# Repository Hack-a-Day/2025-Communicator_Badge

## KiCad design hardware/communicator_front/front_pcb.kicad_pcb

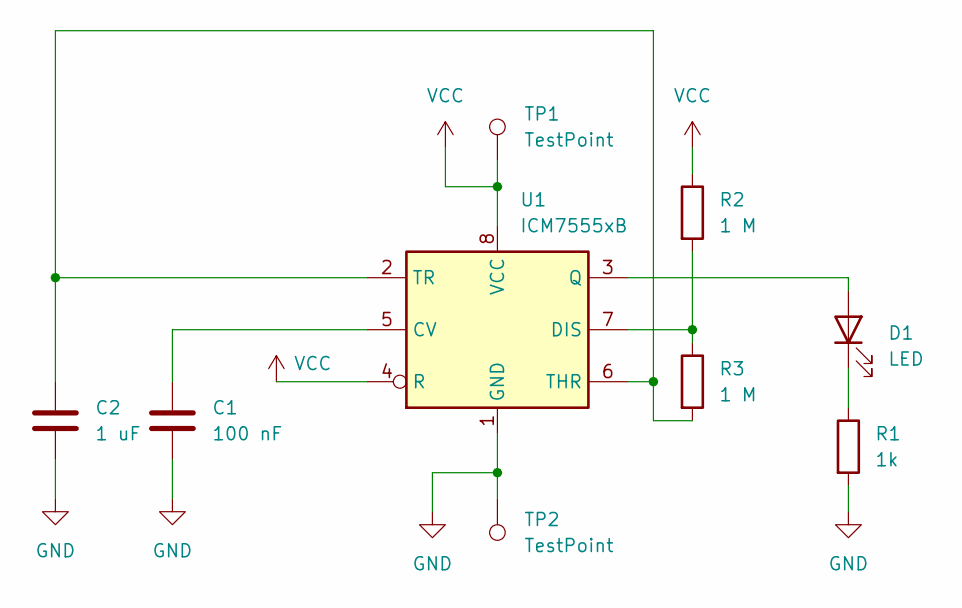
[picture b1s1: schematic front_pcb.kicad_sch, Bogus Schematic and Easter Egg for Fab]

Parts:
C1: 100 nF; C_0805_2012Metric_Pad1.18x1.45mm_HandSolder
C2: 1 uF; C_0805_2012Metric_Pad1.18x1.45mm_HandSolder
D1: LED; LED_0805_2012Metric_Pad1.15x1.40mm_HandSolder
R1: 1k; R_0805_2012Metric_Pad1.20x1.40mm_HandSolder
R2, R3: 1 M; R_0805_2012Metric_Pad1.20x1.40mm_HandSolder
TP1, TP2: TestPoint; TestPoint_Pad_2.5x2.5mm
U1: ICM7555xB; SOIC-8_3.9x4.9mm_P1.27mm

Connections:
GND: C1.2, C2.2, R1.2, TP2.1, U1.1 (GND)
unnamed: D1.2 (A), U1.3 (Q)
unnamed: D1.1 (K), R1.1
unnamed: C1.1, U1.5 (CV)
unnamed: R2.2, R3.1, U1.7 (DIS)
unnamed: C2.1, R3.2, U1.2 (TR), U1.6 (THR)
VCC: R2.1, TP1.1, U1.4 (R), U1.8 (VCC)

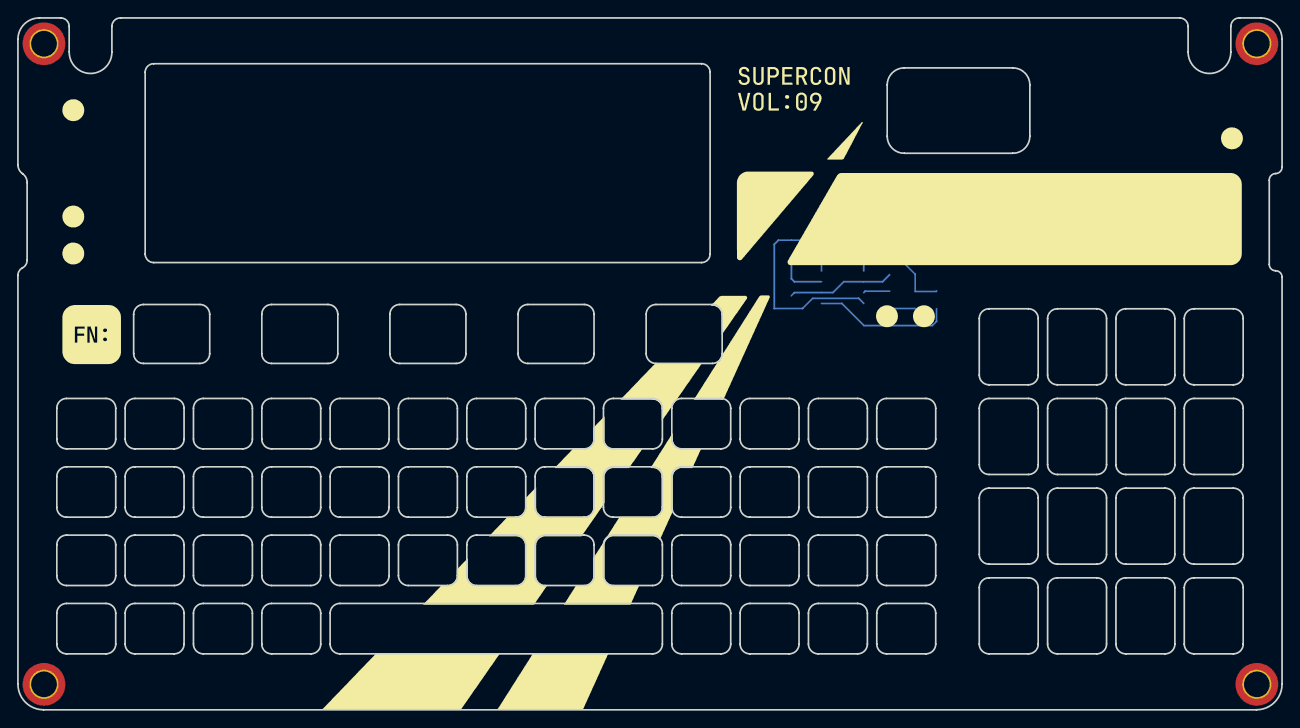
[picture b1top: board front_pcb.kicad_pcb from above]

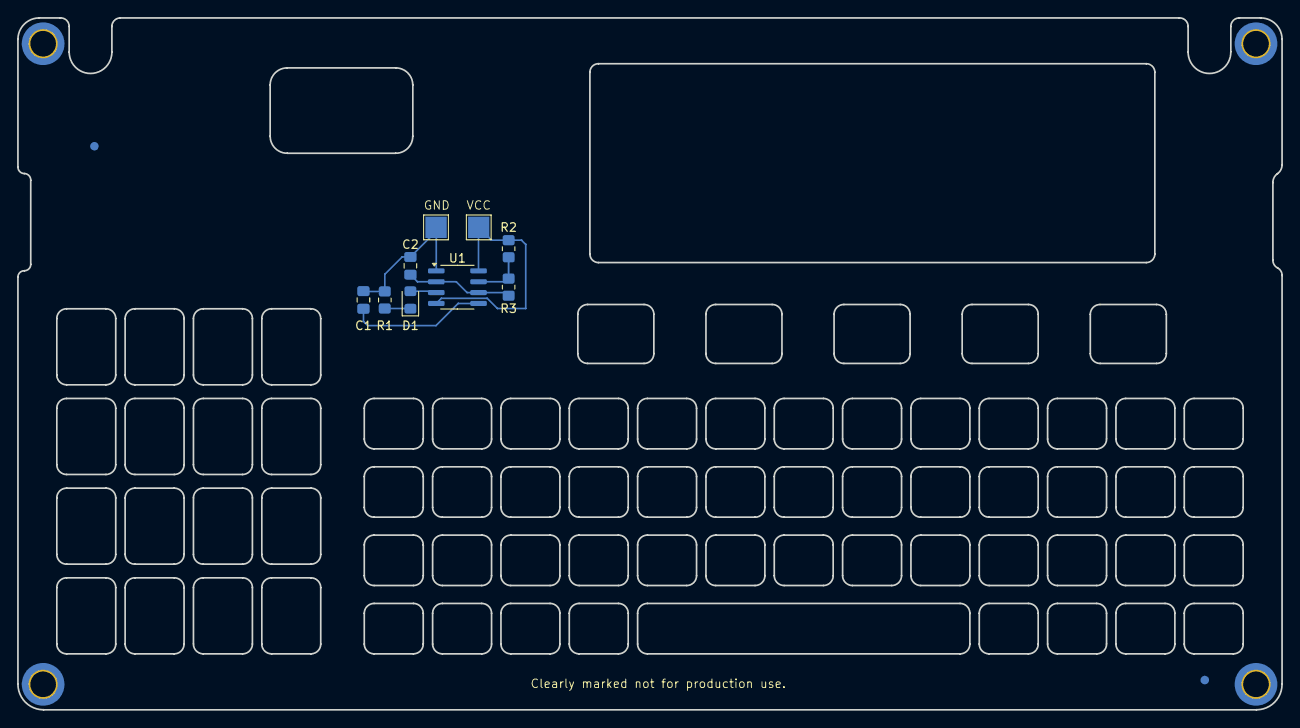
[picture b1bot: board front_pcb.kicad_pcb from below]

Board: 2 copper layers, 148.0 x 81.0 mm, 9 parts (9 on the bottom side), 7 nets.

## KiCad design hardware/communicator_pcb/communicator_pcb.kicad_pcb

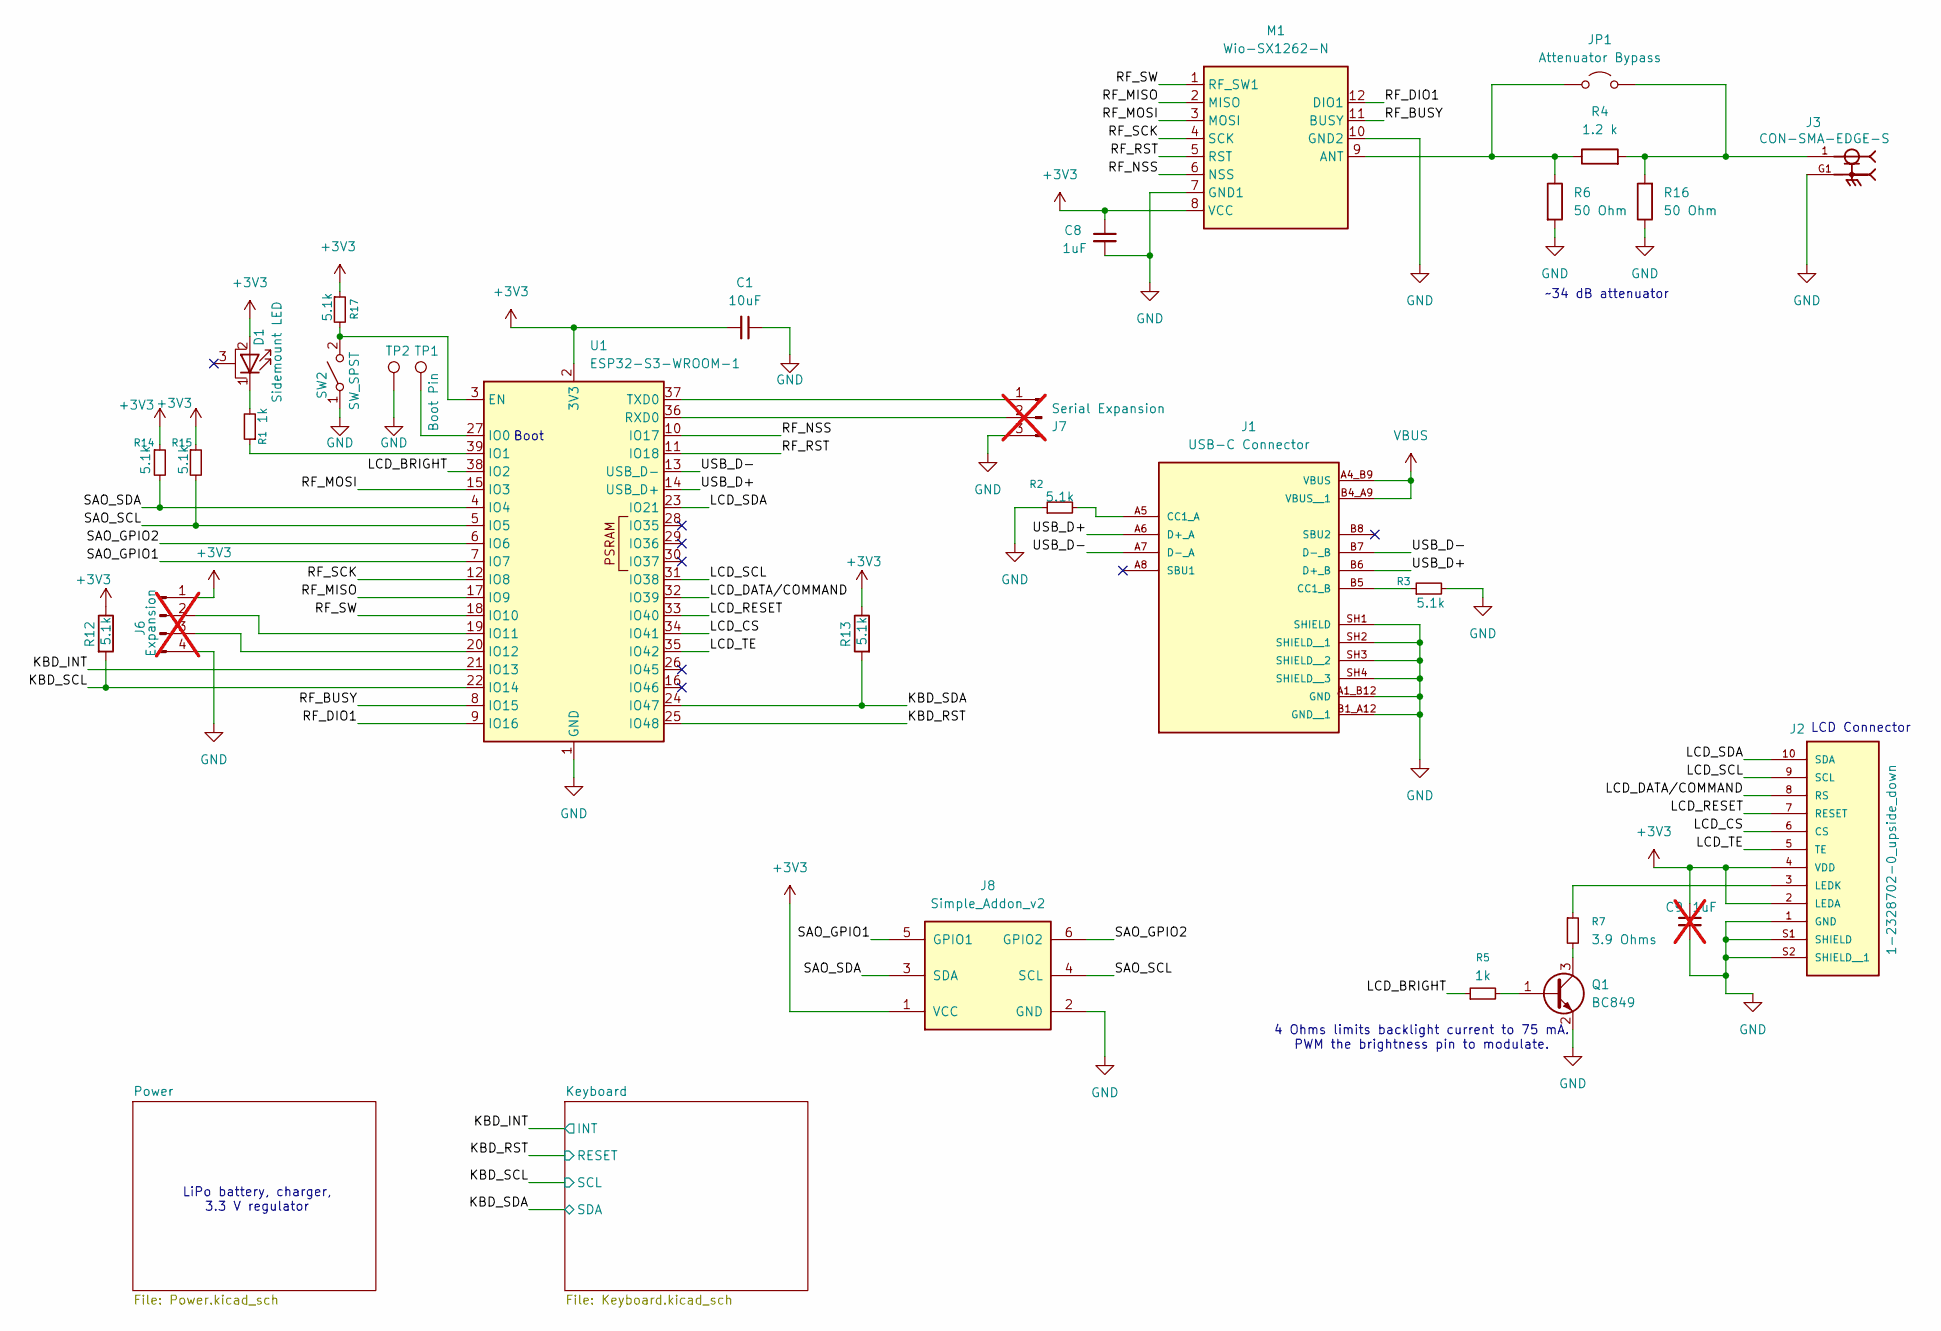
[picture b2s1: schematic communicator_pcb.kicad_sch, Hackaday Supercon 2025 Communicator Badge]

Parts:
C1: 10uF; C_0603_1608Metric
C8: 1uF; C_0603_1608Metric
C9: 1uF; C_0603_1608Metric; not fitted
D1: Sidemount LED; WL-SMSW_1204
J1: USB-C Connector; AMPHENOL_12402012E212A; PARTREV 4
J2: 1-2328702-0_upside_down; TE_1-2328702-0; PARTREV 5
J3: CON-SMA-EDGE-S; RFSOLUTIONS_CON-SMA-EDGE-S; PARTREV 1
J6: Expansion; PinSocket_1x04_P2.54mm_Vertical; not fitted
J7: Serial Expansion; PinHeader_1x03_P2.54mm_Vertical; not fitted
J8: Simple_Addon_v2; Simple_Addon_v2-BADGE-2x3
JP1: Attenuator Bypass; SolderJumper-2_P1.3mm_Open_RoundedPad1.0x1.5mm
M1: Wio-SX1262-N; Wio1262-N
Q1: BC849; SOT-23
R1, R5: 1k; R_0603_1608Metric
R2, R3, R12, R13, R14, R15, R17: 5.1k; R_0603_1608Metric
R4: 1.2 k; R_0603_1608Metric_Pad0.98x0.95mm_HandSolder
R6, R16: 50 Ohm; R_0603_1608Metric_Pad0.98x0.95mm_HandSolder
R7: 3.9 Ohms; R_0603_1608Metric
SW2: SW_SPST; SW_Tactile_SPST_NO_Straight_CK_PTS636Sx25SMTRLFS
TP1: Boot Pin; TestPoint_Pad_D1.5mm
TP2: TestPoint; TestPoint_Pad_D1.5mm
U1: ESP32-S3-WROOM-1

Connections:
+3V3: C1.2, C8.1, C9.1, D1.2 (A), J2.2 (LEDA), J2.4 (VDD), J6.1, J8.1 (VCC), M1.8 (VCC), R12.1, R13.1, R14.1, R15.1, R17.1, U1.2 (3V3); also elsewhere on the board
/KBD_INT: U1.21 (IO13); also elsewhere on the board
/KBD_RST: U1.25 (IO48); also elsewhere on the board
/KBD_SCL: R12.2, U1.22 (IO14); also elsewhere on the board
/KBD_SDA: R13.2, U1.24 (IO47); also elsewhere on the board
/LCD_BRIGHT: R5.1, U1.38 (IO2)
/LCD_CS: J2.6 (CS), U1.34 (IO41)
/LCD_DATA/COMMAND: J2.8 (RS), U1.32 (IO39)
/LCD_RESET: J2.7 (RESET), U1.33 (IO40)
/LCD_SCL: J2.9 (SCL), U1.31 (IO38)
/LCD_SDA: J2.10 (SDA), U1.23 (IO21)
/LCD_TE: J2.5 (TE), U1.35 (IO42)
/RF_BUSY: M1.11 (BUSY), U1.8 (IO15)
/RF_DIO1: M1.12 (DIO1), U1.9 (IO16)
/RF_MISO: M1.2 (MISO), U1.17 (IO9)
/RF_MOSI: M1.3 (MOSI), U1.15 (IO3)
/RF_NSS: M1.6 (NSS), U1.10 (IO17)
/RF_RST: M1.5 (RST), U1.11 (IO18)
/RF_SCK: M1.4 (SCK), U1.12 (IO8)
/RF_SW: M1.1 (RF_SW1), U1.18 (IO10)
/SAO_GPIO1: J8.5 (GPIO1), U1.7 (IO7)
/SAO_GPIO2: J8.6 (GPIO2), U1.6 (IO6)
/SAO_SCL: J8.4 (SCL), R15.2, U1.5 (IO5)
/SAO_SDA: J8.3 (SDA), R14.2, U1.4 (IO4)
/USB_D+: J1.A6 (D+_A), J1.B6 (D+_B), U1.14 (USB_D+)
/USB_D-: J1.A7 (D-_A), J1.B7 (D-_B), U1.13 (USB_D-)
GND: C1.1, C8.2, C9.2, J1.A1_B12 (GND), J1.B1_A12 (GND__1), J1.SH1 (SHIELD), J1.SH2 (SHIELD__1), J1.SH3 (SHIELD__2), J1.SH4 (SHIELD__3), J2.1 (GND), J2.S1 (SHIELD), J2.S2 (SHIELD__1), J3.G1, J3.G2, J3.G3, J3.G4, J6.4, J7.3, J8.2 (GND), M1.7 (GND1), M1.10 (GND2), Q1.2 (E), R2.1, R3.2, R6.2, R16.1, SW2.1 (A), TP2.1, U1.1 (GND), U1.40 (GND), U1.41 (GND); also elsewhere on the board
unnamed: D1.1 (K), R1.2
unnamed: J1.A5 (CC1_A), R2.2
unnamed: J1.B5 (CC1_B), R3.1
unnamed: J2.3 (LEDK), R7.1
unnamed: J6.2, U1.19 (IO11)
unnamed: J6.3, U1.20 (IO12)
unnamed: J7.1, U1.37 (TXD0)
unnamed: J7.2, U1.36 (RXD0)
unnamed: JP1.1 (A), M1.9 (ANT), R4.1, R6.1
unnamed: J3.1, JP1.2 (B), R4.2, R16.2
unnamed: Q1.1 (B), R5.2
unnamed: Q1.3 (C), R7.2
unnamed: R17.2, SW2.2 (B), U1.3 (EN)
unnamed: TP1.1, U1.27 (IO0)
unnamed: R1.1, U1.39 (IO1)
VBUS: J1.A4_B9 (VBUS), J1.B4_A9 (VBUS__1); also elsewhere on the board

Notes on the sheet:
~34 dB attenuator
LCD Connector
LiPo battery, charger, 3.3 V regulator
Boot
4 Ohms limits backlight current to 75 mA. PWM the brightness pin to modulate.

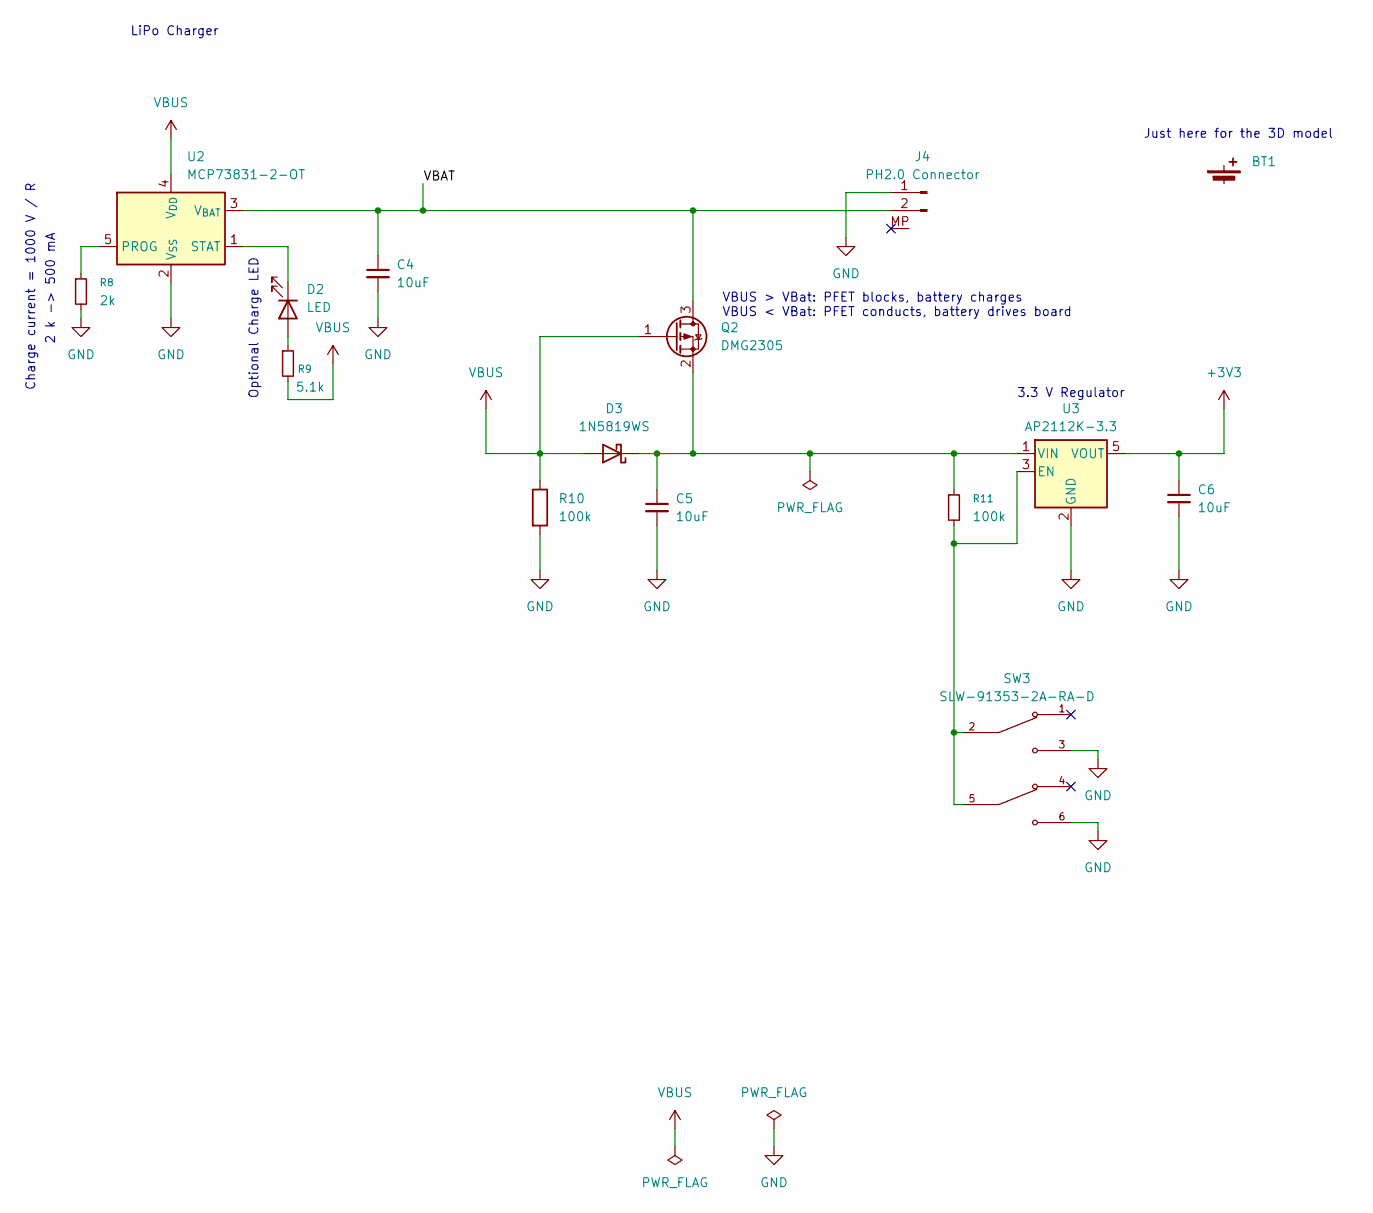
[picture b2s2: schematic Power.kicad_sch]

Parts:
BT1: BatteryMockup
C4, C5, C6: 10uF; C_0603_1608Metric
D2: LED; LED_0805_2012Metric
D3: 1N5819WS; D_SOD-323
J4: PH2.0 Connector; JST_PH_S2B-PH-SM4-TB_1x02-1MP_P2.00mm_Horizontal
Q2: DMG2305; SOT-23
R8: 2k; R_0603_1608Metric
R9: 5.1k; R_0603_1608Metric
R10, R11: 100k; R_0603_1608Metric
SW3: SLW-91353-2A-RA-D; SW_SLW-91353-2A-RA-D; PARTREV 1.01
U2: MCP73831-2-OT; SOT-23-5
U3: AP2112K-3.3; SOT-23-5

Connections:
+3V3: C6.1, U3.5 (VOUT); also elsewhere on the board
/Power/VBAT: C4.1, J4.2, Q2.3 (D), U2.3 (V_{BAT})
GND: C4.2, C5.2, C6.2, J4.1, R8.2, R10.2, SW3.3, SW3.6, U2.2 (V_{SS}), U3.2 (GND); also elsewhere on the board
unnamed: D2.2 (A), R9.1
unnamed: D2.1 (K), U2.1 (STAT)
unnamed: C5.1, D3.1 (K), Q2.2 (S), R11.1, U3.1 (VIN)
unnamed: R8.1, U2.5 (PROG)
unnamed: R11.2, SW3.2, SW3.5, U3.3 (EN)
VBUS: D3.2 (A), Q2.1 (G), R9.2, R10.1, U2.4 (V_{DD}); also elsewhere on the board

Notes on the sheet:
Optional Charge LED
Just here for the 3D model
VBUS > VBat: PFET blocks, battery charges VBUS < VBat: PFET conducts, battery drives board
Charge current = 1000 V / R
2 k -> 500 mA
LiPo Charger
3.3 V Regulator

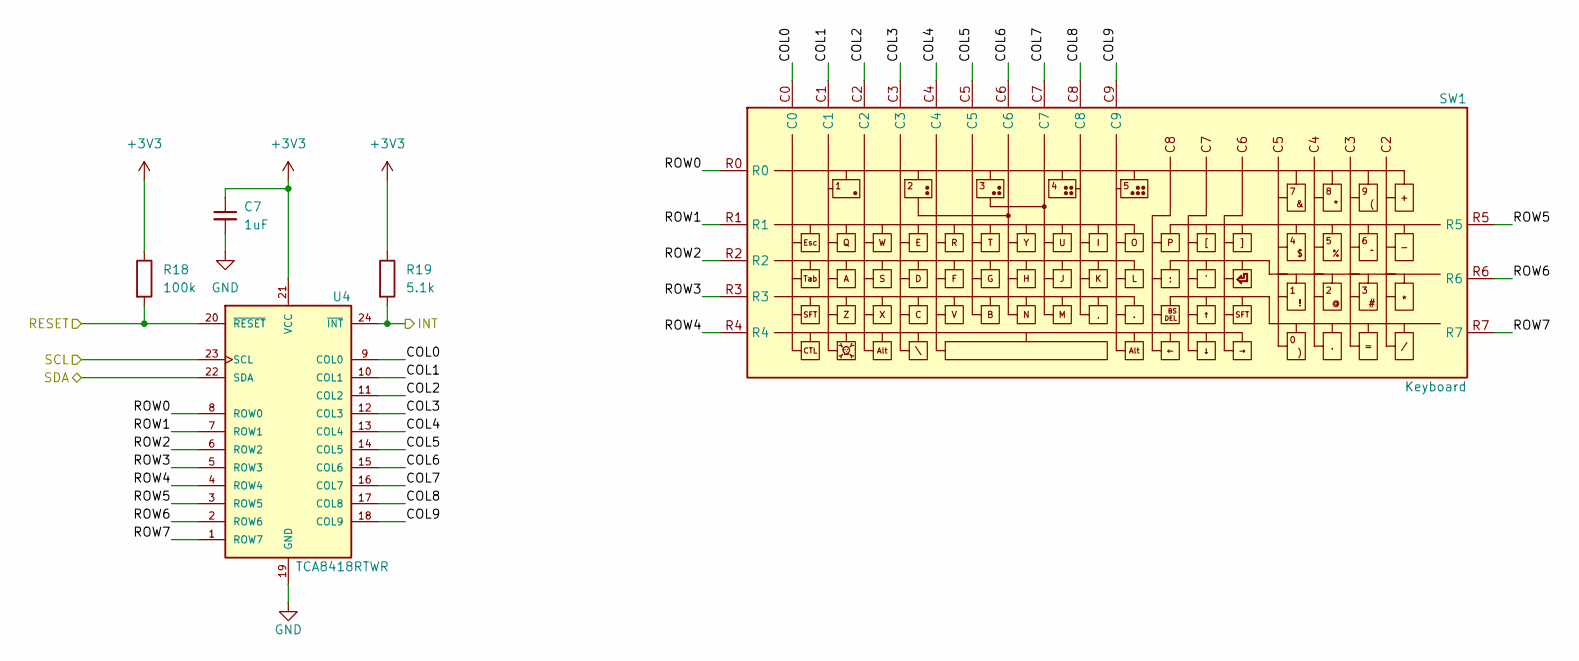
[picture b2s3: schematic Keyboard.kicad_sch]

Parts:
C7: 1uF; C_0603_1608Metric
R18: 100k; R_0603_1608Metric
R19: 5.1k; R_0603_1608Metric
SW1: Keyboard
U4: TCA8418RTWR; VQFN-24-1EP_4x4mm_P0.5mm_EP2.5x2.5mm; PARTREV G

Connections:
+3V3: C7.1, R18.1, R19.1, U4.21 (VCC); also elsewhere on the board
/KBD_INT: R19.2, U4.24 (~INT); also elsewhere on the board
/KBD_RST: R18.2, U4.20 (~RESET); also elsewhere on the board
/KBD_SCL: U4.23 (SCL); also elsewhere on the board
/KBD_SDA: U4.22 (SDA); also elsewhere on the board
/Keyboard/COL0: SW1.C0, U4.9 (COL0)
/Keyboard/COL1: SW1.C1, U4.10 (COL1)
/Keyboard/COL2: SW1.C2, U4.11 (COL2)
/Keyboard/COL3: SW1.C3, U4.12 (COL3)
/Keyboard/COL4: SW1.C4, U4.13 (COL4)
/Keyboard/COL5: SW1.C5, U4.14 (COL5)
/Keyboard/COL6: SW1.C6, U4.15 (COL6)
/Keyboard/COL7: SW1.C7, U4.16 (COL7)
/Keyboard/COL8: SW1.C8, U4.17 (COL8)
/Keyboard/COL9: SW1.C9, U4.18 (COL9)
/Keyboard/ROW0: SW1.R0, U4.8 (ROW0)
/Keyboard/ROW1: SW1.R1, U4.7 (ROW1)
/Keyboard/ROW2: SW1.R2, U4.6 (ROW2)
/Keyboard/ROW3: SW1.R3, U4.5 (ROW3)
/Keyboard/ROW4: SW1.R4, U4.4 (ROW4)
/Keyboard/ROW5: SW1.R5, U4.3 (ROW5)
/Keyboard/ROW6: SW1.R6, U4.2 (ROW6)
/Keyboard/ROW7: SW1.R7, U4.1 (ROW7)
GND: C7.2, U4.19 (GND), U4.25 (EP); also elsewhere on the board

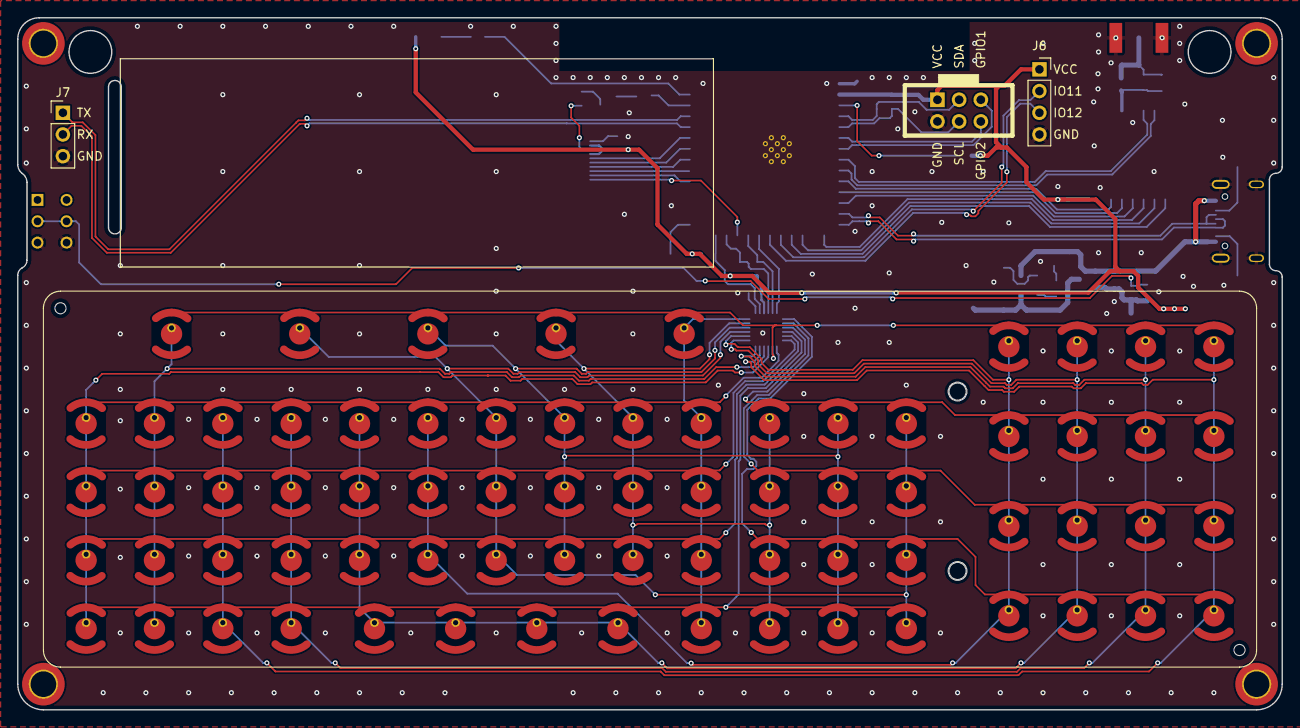
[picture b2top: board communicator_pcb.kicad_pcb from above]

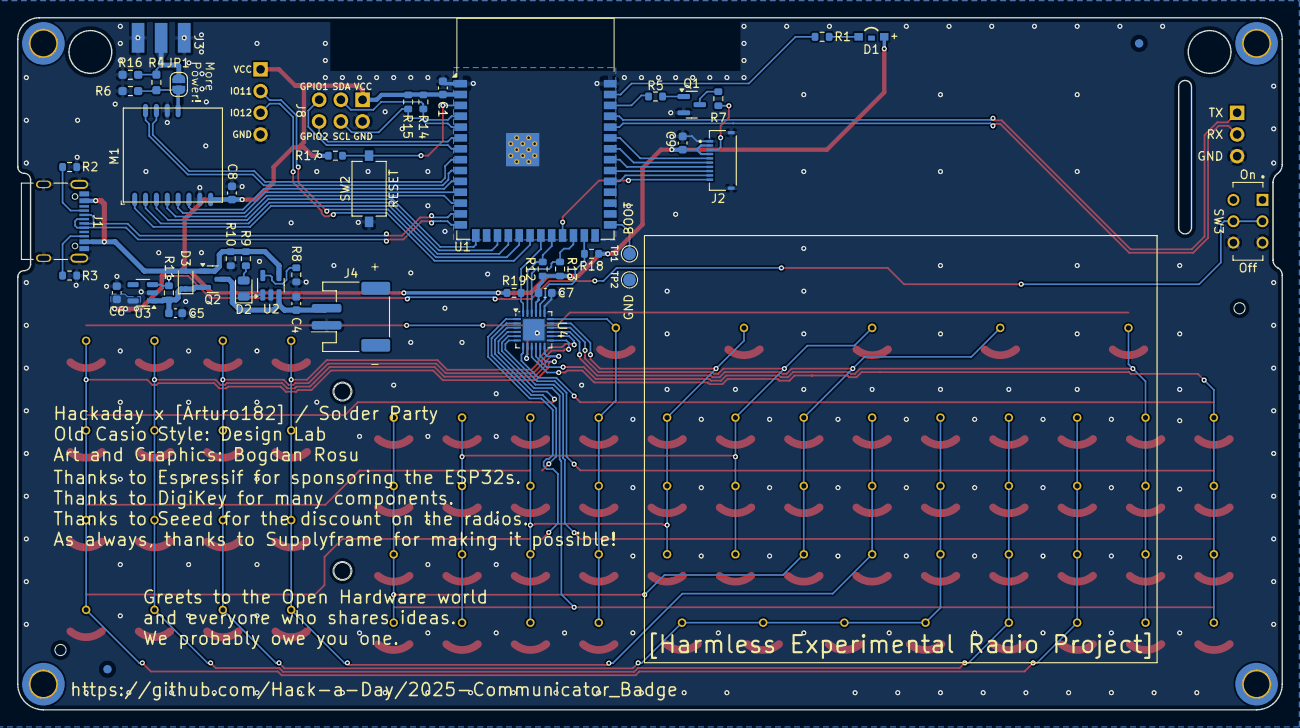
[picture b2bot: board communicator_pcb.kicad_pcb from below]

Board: 2 copper layers, 148.0 x 81.0 mm, 50 parts (46 on the bottom side), 67 nets.

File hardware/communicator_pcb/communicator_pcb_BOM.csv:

Reference	Qty	Value	DNP	Footprint	Part	Datasheet	
C1,C4,C5,C6	4	10uF		Capacitor_SMD:C_0603_1608Metric		~	
C7,C8	2	1uF		Capacitor_SMD:C_0603_1608Metric		~	
D1	1	Sidemount LED		wurth_led_155124YS73200:WL-SMSW_1204	https://www.digikey.de/en/products/detail/w%C3%BCrth-elektro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	https://www.we-online.com/components/products/datasheet/1551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	
D2	1	LED		LED_SMD:LED_0805_2012Metric		~	
D3	1	1N5819WS		Diode_SMD:D_SOD-323	https://www.digikey.de/en/products/detail/shenzhen-slkormicr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	https://datasheet.lcsc.com/lcsc/2204281430_Guangdong-Hottech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	
J1	1	USB-C Connector		amphenol_12402012E212A:AMPHENOL_12402012E212A	https://www.digikey.de/en/products/detail/amphenol-cs-commer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	https://cdn.amphenol-cs.com/media/wysiwyg/files/drawing/1240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	
J2	1	1-2328702-0_upside_down		TE_1-2328702-0:TE_1-2328702-0	https://www.digikey.de/en/products/detail/te-connectivity-am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		
J3	1	CON-SMA-EDGE-S		CON_SMA_EDGE_S:RFSOLUTIONS_CON-SMA-EDGE-S			
J4	1	PH2.0 Connector		Connector_JST:JST_PH_S2B-PH-SM4-TB_1x02-1MP_P2.00mm_Horizontal	https://www.digikey.com/en/products/detail/jst-sales-america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	https://www.jst-mfg.com/product/pdf/eng/ePH.pdf	
J8	1	Simple_Addon_v2		Simple_Addon_v2:Simple_Addon_v2-BADGE-2x3	Where are we getting these?  Can we get the nice shrouded onew?	https://hackaday.io/project/175182-simple-add-ons-sao	
M1	1	Wio-SX1262-N		Wio1262:Wio1262-N	Order from Seeed	https://files.seeedstudio.com/products/SenseCAP/Wio_SX1262/W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	
Q1	1	BC849		Package_TO_SOT_SMD:SOT-23	https://www.digikey.de/en/products/detail/onsemi/BC849CLT1G/1476052	http://www.infineon.com/dgdl/Infineon-BC847SERIES_BC848SERIE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	
Q2	1	DMG2305		Package_TO_SOT_SMD:SOT-23	https://www.digikey.de/en/products/detail/diodes-incorporate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	https://www.diodes.com/assets/Datasheets/DMG2301L.pdf	
R1,R5	2	1k		Resistor_SMD:R_0603_1608Metric		~	
R2,R3,R9,R12,R13,R14,R15,R17,R19	9	5.1k		Resistor_SMD:R_0603_1608Metric		~	
R4	1	1.2 k				Resistor_SMD:R_0603_1608Metric_Pad0.98x0.95mm_HandSolder	~
R6,R16	2	50 Ohm				Resistor_SMD:R_0603_1608Metric_Pad0.98x0.95mm_HandSolder	~
R7	1	3.9 Ohms		Resistor_SMD:R_0603_1608Metric		~	
R8	1	2k		Resistor_SMD:R_0603_1608Metric		~	
R10,R11,R18	3	100k		Resistor_SMD:R_0603_1608Metric		~	
SW1	1	Keyboard		Keyboard:Keyboard	Arturo's keyboard		
SW2	1	SW_SPST		Button_Switch_SMD:SW_Tactile_SPST_NO_Straight_CK_PTS636Sx25SMTRLFS	https://www.digikey.de/en/products/detail/c-k/PTS636SK25FSMT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 	~	
SW3	1	SLW-91353-2A-RA-D		SLW_1353_2A_RA_D:SW_SLW-91353-2A-RA-D	https://www.digikey.de/en/products/detail/same-sky-formerly-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	https://www.cuidevices.com/product/resource/digikeypdf/slw-9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	
U1	1	ESP32-S3-WROOM-1		RF_Module:ESP32-S3-WROOM-1	From Espressif	https://www.espressif.com/sites/default/files/documentation/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	
U2	1	MCP73831-2-OT		Package_TO_SOT_SMD:SOT-23-5	https://www.digikey.de/en/products/detail/microchip%20techno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	http://ww1.microchip.com/downloads/en/DeviceDoc/20001984g.pdf	
U3	1	AP2112K-3.3		Package_TO_SOT_SMD:SOT-23-5	https://www.digikey.de/en/products/detail/diodes%20incorpora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	https://www.diodes.com/assets/Datasheets/AP2112.pdf	
U4	1	TCA8418RTWR		Package_DFN_QFN:VQFN-24-1EP_4x4mm_P0.5mm_EP2.5x2.5mm	https://www.digikey.de/en/products/detail/texas-instruments/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	https://www.ti.com/lit/ds/symlink/tca8418.pdf	
							
							
C9	1	1uF	DNP			Capacitor_SMD:C_0603_1608Metric	~
J6	1	Expansion	DNP			Connector_PinSocket_2.54mm:PinSocket_1x04_P2.54mm_Vertical	~
J7	1	Serial Expansion	DNP			Connector_PinHeader_2.54mm:PinHeader_1x03_P2.54mm_Vertical	~

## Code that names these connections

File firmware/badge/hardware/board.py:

from machine import Pin, Signal, PWM

# https://docs.micropython.org/en/latest/esp32/quickref.html

DEBUG_LED = Signal(Pin(1, Pin.OUT), invert=True)
GPIO_0 = Pin(0, Pin.IN)

# Keyboard I2C
KBD_SCL = Pin(14)
KBD_SDA = Pin(47)
KBD_INT = Pin(13, Pin.IN)
KBD_RST = Pin(48, Pin.OUT)

# LCD I2C
LCD_SCL = Pin(38)
LCD_SDA = Pin(21)
LCD_RST = Pin(40, Pin.OUT)
LCD_CS = Pin(41, Pin.OUT)
LCD_TE = Pin(42, Pin.OUT)
#LCD_BACKLIGHT = PWM(Pin(2)) # Already defined is in `lvgl_setup.py`
LCD_DATA_CMD = Pin(39, Pin.OUT)

# Radio SPI + Extras
RF_NSS = 17  # Pin(17, Pin.IN)  # CS
RF_RST = Pin(18)
RF_MOSI = 3  # Pin(3, Pin.OUT)
RF_SCK = 8  # Pin(8, Pin.OUT)
RF_MISO = 9  # Pin(9, Pin.IN)
RF_SW = Pin(10, Pin.OUT, value=1)  # Dir ?
RF_BUSY = Pin(15, Pin.IN)
RF_DIO1 = Pin(16)  # Dir ?

# SAO
SAO_SCL = Pin(5)
SAO_SDA = Pin(4)
SAO_GPIO1 = Pin(7)
SAO_GPIO2 = Pin(6)

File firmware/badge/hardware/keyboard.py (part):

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        try:
            self.i2c.writeto_mem(
                self.ADDR, 0x1D, b"\xff"
            )  # KP_GPIO1 all ROW7:0 to KP matrix
            self.i2c.writeto_mem(
                self.ADDR, 0x1E, b"\xff"
            )  # KP_GPIO2 all COL7:0 to KP matrix
            self.i2c.writeto_mem(
                self.ADDR, 0x1F, b"\x03"
            )  # KP_GPIO3 all COL9:8 to KP matrix
            self.i2c.writeto_mem(
                self.ADDR, 0x01, b"\x91"
            )  # CFG Set the KE_IEN, INT_CFG, and AI bits
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
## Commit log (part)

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2025-10-23 initial commit. pulling in datasheets and vendor docs
2025-10-23 communicator badge front panel
2025-10-23 pulling in PCB
2025-10-23 update readme with better photos
2025-10-23 fixed outline issues on front pcb
2025-10-23 Add initial LoRa dense deployment firmware (POC)
    Introduce firmware for Supercon 2025 badge supporting dense LoRa mesh networking. Includes MAC protocol implementation (lora_mac.py), SX1262 hardware abstraction (lora_hal.py), configuration presets 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
2025-10-24 Fixes #3: removing redundant SMA 3D model
    Thanks, [thzinc]!
2025-10-24 importing the badge gasket and back parts
2025-10-24 adding in step, freecad, dxf, and svg conversions
2025-10-31 Add firmware and associated tooling
2025-10-31 add in user application area
2025-10-31 Fixed mismapped Shift+0 from . to )
2025-10-31 Replaces the period when shift is active with the right Paren, as on the silkscreen of the keyboard
2025-10-31 Switch pip install to requirements.txt
2025-10-31 yeah, -r is important
2025-10-31 headshot fix.
2025-10-31 Fix keyboard mapping for `)` (Shift+0)
2025-10-31 Rip out submodules and copy in crc lib directly. Move nametag label rename
2025-10-31 Fix incorrect command for copying from a folder to the badge
2025-10-31 Submodule removal readme fix
2025-10-31 clean up compile notes
2025-10-31 Add null check before scrolling page
    avoid crashing the chat app when page is empty and trying to scroll to the Latest
2025-10-31 Updating push to ignore __pycache__ as well as recursivly delete dirs
2025-10-31 Fix talks entry
    * Fix typo in last name
    * Update image
2025-10-31 [update.py] rmdir fix
2025-10-31 [update.py] rmdir fix re re re redux
2025-10-31 Add headshot to the nametag
2025-10-31 Remove "1" from nametag option.
2025-10-31 move nametag show image to false instead of 1.
2025-10-31 Set the config to show the image when selected.
2025-10-31 set timestamp on seen messages, fix early expiration bug
2025-10-31 When the name changes update the preview
2025-10-31 Cats!
2025-11-01 fix update script to not break on directory removal
2025-11-01 [i2c][fix] initialize keyboard correctly
2025-11-01 Set explicit IDs for i2c controllers
2025-11-01 add ability to hide nametag image
2025-11-01 Fix wrong indentation causing soft locks in talks app
2025-11-01 [fig] config override causes crash
2025-11-01 2 and 3 line labels
2025-11-01 easy Topic switching
    - removes id if alias is specified
    - adds topic seeking (change topic, skipping empty) using left / right arrows
    - updates chat view on topic switch
    - updates chat view on switch_to_foreground
2025-11-01 Fix lvgl build instructions
2025-11-01 Save ui page in self.p in user apps, just like nametag app does
2025-11-01 Added "venv/" to .gitignore to match instructions in readme
2025-11-01 Need more dog headshots! Here's one.
2025-11-01 [mcblockface] it's gaem
2025-11-01 Multiplayer Rock/Paper/Scissors game.
2025-11-01 Fixed the readability problem with the firmware README
2025-11-01 [mcblockface] fixes
2025-11-01 Expanding color options in styles configuration file.
2025-11-01 Handle index error parsing received packets
2025-11-01 Adding support for interest levels and associated coloring for each interest level.
2025-11-01 Expanding talks application to track and save interest levels per topic.
2025-11-01 hot_topic initial pass
2025-11-01 Possibly improve the stability of lvgl by moving its event loop to asyncio
2025-11-01 Adding AppManager to user apps.
    AppManager is a replacement for the hard-coded User AppMenu app that
    automatically discovers application modules added to the apps directory.
    Simply add some metadata constants to your app module and copy the
    module.py into the apps directory on your device. AppManager will find
    the new module and add the app to its dynamic application menu on reset.
2025-11-02 Add support to send config messages
2025-11-02 Fixing naming used on custom colors to not conflict or imply correlation with Hackaday style guies.
2025-11-02 Add user apps: spectrum analyzer, hardware monitor, screensaver, and snake game
2025-11-02 Add Shift+Arrow to scroll the config
2025-11-02 PR feedback
2025-11-02 one more line to move
2025-11-02 Create a fish app for displaying an animated aquarium
2025-11-02 Shifting to using a unique CSV file for tracking schedule interests.
2025-11-02 Moving tracking CSV file for interests to the data folder.
2025-11-02 Move the fish app to user_apps and add a readme
2025-11-02 Remove prints from fish app
2025-11-02 Fix alias display bug in Rock/Paper/Scissors app.
2025-11-02 Ready for PR for TyperRoyale
2025-11-02 AppManager auto-detect all apps
2025-11-02 OTA updates
2025-11-02 Game of Life simulation
2025-11-02 Added user app: 'Supercon Text Adventure'
2025-11-03 Add basic air quality app
2025-11-03 Don't push .git
2025-11-03 [airquality] Fix crash on app exit with no sensors
2025-11-03 Add SuperStarTrek (SST3) game port.
2025-11-08 Limits ugit to pull only appropriate folder
2025-11-08 Update README with WiFi credentials instructions
    Added instructions to edit WiFi credentials in README.
2025-12-24 add MIT license
    closes #54
2025-12-29 Fix LoRa frame checksum calculation and validation
    During frame serialization checksum should be calculated for data following the Flags/TTL byte;
    During frame validation calced_checksum needs to be converted to bytes to compare to claimed_checksum
2025-12-29 Change `update.py` shebang to /usr/bin/env for better portability
2026-02-14 Add AppManager to main, update docs to match, update demo apps from App name
2026-02-14 README fix
2026-02-14 Various upgrades: * Talks: Stage button changed to update interest * Debug LED defaults off, only turns on for Tx * Chat and RPS TTL incremented significantly
2026-02-14 Add ImHex pattern for parsing LoRa packets
2026-02-14 Add ImHex screenshot to readme
2026-04-29 Default app manager in main to make it easier to add custom apps (#56)
    * Add AppManager to main, update docs to match, update demo apps from App name
    * README fix
2026-04-29 Talks interest button, default led off: (#57)
    * Talks: Stage button changed to update interest
    * Debug LED defaults off, only turns on for Tx
    * Chat and RPS TTL incremented significantly
2026-05-13 Remove Supercon headshots (leave cats)
2026-05-13 Add Europe headshots
2026-05-13 Adjust schedule app for Europe
2026-05-13 Add schedule CSV for Europe
2026-05-13 change frequency to 869.525 for EU
    note: here, we have just one channel, so the channel-changing
    infrastructure is moot. Should remove.
2026-05-13 rebranding to Lecco, removing frequency selector
2026-05-13 cycled talk colors back to default background
2026-05-14 Remove stale apps
2026-05-14 Tweak app_manager messages
2026-05-14 Add new demo app, merge in user apps
2026-05-14 change UI for config app, made scrolling more intuitive
2026-05-15 flash this image
2026-05-15 quick flasher routine
2026-05-16 Fixed "edit" function in config_manager
    Allows to edit values in Config Manager.
2026-05-16 Edit Button for Config fix
    The edit button doesnt work, seems like the edit routine was removed accidentally
2026-05-16 Adding a clock to the infobar of menu
2026-05-17 Added a flipped mode to Name Tag
2026-05-21 feat: implement CLI application for serial interaction and add hardware-in-the-loop test suite
2026-05-21 feat: add LoRa CLI commands and HITL testing infrastructure for firmware validation
2026-05-21 feat: implement modular CLI application and shell command infrastructure with testing mocks
2026-05-21 Implement Flipper-Zero style CLI wrappers, apps, and test suite
2026-05-21 feat: add badge CLI shell with storage, system info, and tab completion features along with unit tests
2026-05-21 feat: implement interactive badge CLI shell with command support for BadUSB, storage, and radio modules
2026-05-21 feat: implement interactive shell and serial terminal command infrastructure for badge CLI
2026-05-21 feat: implement ShellGuiApp for terminal emulation and add associated unit tests and mock badge infrastructure
2026-05-21 feat: implement ShellGuiApp for on-screen terminal interaction and add to main menu
2026-05-21 feat: add firmware build and test workflows for CI/CD integration
2026-05-21 feat: enhance CLI input handling and command display formatting
2026-05-21 feat: add build and deployment instructions for the badge firmware
2026-05-21 feat: update APPMOD_DENYLIST and add clear command to MetaCommands
2026-05-21 feat: streamline chat command message sending and enhance wardriving command tests
2026-05-21 fix(cli): handle stdin without fileno in CliApp poll setup
2026-05-21 feat(tests): enhance CLI tests and add new test cases for command handling
2026-05-22 feat(cli): implement wardriving command group with Wi-Fi and BLE scanning capabilities
2026-05-22 feat(cli): enhance CLI input handling and improve terminal rendering in Shell GUI
2026-05-22 feat: Enhance BLE functionality with scanning and advertising commands
    - Added BLE advertising capabilities to the `BleCommands` class, allowing users to start and stop advertising with customizable names.
    - Implemented a method to extract local names from advertisement data and build advertisement payloads.
    - Enhanced the scanning command to display additional information, including device names and markers.
    - Introduced a new command to display the local BLE MAC address.
    - Updated the main application to support hardware-in-the-loop (HITL) mode, enabling selective app loading based on configuration.
    - Added a new script for flashing firmware to connected badges with optional HITL mode conf
2026-05-22 feat(wifi): Implement Wi-Fi AP management commands and enhance scanning capabilities
    - Added 'ap' command for managing hotspot/AP mode with options to turn on, off, or check status.
    - Enhanced CLI tests to cover new Wi-Fi AP command functionalities.
    - Introduced fixtures for multi-device Wi-Fi tests, including known SSID and BSSID options.
    - Added tests for Wi-Fi AP command behavior, including password validation and scan stability.
    - Implemented checks for shared BSSID consistency across multiple devices during Wi-Fi scans.
2026-05-22 feat(cli): add Wi-Fi and BLE command enhancements for wardriving and testing
2026-05-22 feat: Enhance CLI with new display and input commands
    - Added `display` command group for rendering text, images, and controlling backlight.
    - Introduced `input` command group for keyboard injection and event dumping.
    - Implemented `radio` command group for low-level SX1262 controls including frequency, power, and spreading factor settings.
    - Added `subghz` command group for raw Sub-GHz packet capture and replay functionality.
    - Created signal recorder and player for handling Sub-GHz packet files.
    - Updated documentation to reflect new command structures and usage.
2026-05-22 Avoid Flipper HITL auto-detection in CI
2026-05-22 Make input dump sweep-safe
2026-06-04 Tidy feature list in README.md
    Updated feature descriptions for clarity and consistency.
2026-06-15 Added set time ui on config_manager app
    Allows the user to set date time on the RTC module that can
    be used everywhere to correct attach time.
    This allows users to proper log information and timestamp
    messages for the LoRa network.
2026-06-16 Created a registry of raw listeners on net/net
    This allow applications to subscribe to raw LoRa packets.
    The current net framework has a set frame that does not allow
    meshcore or other protocols to be implemented on top. This is
    also useful for packet analysers and other apps.
    Just good for hacking in general. :)
2026-06-16 Modified error message handling to only error out if raw callbacks did not accept the message
